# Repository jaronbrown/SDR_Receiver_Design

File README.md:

# Walla Walla University ENGR357 SDR Design Winter 2024

## Goals
- Continuous Coverage from 5-30 MHz and AM coverage (540-1700 kHz)
- Tune to AM by mixing up to 10.7 MHz then using the Tayloe detector to down-sample to 0-48 kHz

## Design
 - Incorporates a two stage mixing approach in order to achieve wider bandwidth with Si5351 quadrature limitations 
 - Utilizes a Tayloe detector for down-conversion of RF signals.
 - Optional second mixer to bring up AM frequencies (540-1700 kHz) so they can be sampled by Tayloe detector.
 - Input Stage: Automatic Band Pass Filters with optional AM mixer. Includes antenna ground isolation.
 - Output Stage: Quadrature signals amplified with 84 kHz low pass filter. Sampled directly with on-board ADC (48 kHz Nyquist) or output over 3.5mm audio jack. The larger LPF passband (84 kHz) minimizes ripple.
 - Raspberry Pi Pico W Controller with LDO (TPS7A8001DRBR) for cleaner +4V5 (derived from +5V USB).
 - H/W Controlled BPF multiplexors, i2c controlled 3-output VLO (Si5351), and i2s compatible ADC (PCM1808PWR).

## ltspice Simulations
Various core elements of the design were simulated to test their functionality. Notable simulations include a [Monte Carlo simulation](spice/BPF_monte_carlo.asc) of the three bandpass filters (frequency response shown below) to determine effects of component tolerances and a [simulation of the Tayloe detector](spice/Tayloe_test.asc), along with its "differential" amplifiers. The Tayloe detector input is a 1 $\mu V$ sinewave and the output (of the I channel) can be seen in the graph below. In the actual implementation, there is a 1 $\mu F$ blocking capacitor before the ADC and audio jack, but this is omitted for sake of simulation. This would remove the 2.25V DC offset.

Bandpass Filters

Tayloe Detector

## Fabrication Information
The boards tested were fabricated by [JLCPCB](jlcpcb.com). They also installed all the surface-mount components--LCSC part numbers included in schematic. Total fabrication cost (including building the boards) from JLCPCB was about $120 USD for 5 boards. The [build plan](BuildPlan.md) was followed for assembling the boards and testing their functionality. The specifications for the inductors and transformer used, can be found in [Inductors](Inductors.md).

## Software
### Python
The software for the Raspberry Pi Pico W consists of three microPython files: [main.py](python/main.py), [radio.py](python/radio.py), and [si5351.py](python/si5351.py). All three files should be loaded onto the Pico.

The microPython module to control the SI5351, [si5351.py](python/si5351.py), was provided by [https://github.com/thaaraak/Tinypico-Radio/tree/master](https://github.com/thaaraak/Tinypico-Radio/tree/master). Some minor changes were made to the ```outputs_enabled``` setter in order to allow individual clock enabling/disabling--used for the AM mixer local oscillator.

The radio control is handled by [radio.py](python/radio.py) which after initializing a ```Radio```, ```run()``` can be used to parse Quisk commands and automatically control bandpass filter selection (based on frequency) and frequency. The bandpass filters can also be controlled manually by entering "BAND,AUTO" to allow for manual testing and use of the built in bypass capacitor. Frequencies from 4-32 MHz are handled via the HF HIGH/LOW BPFs with a single stage of mixing. Frequencies from 0.4-4 MHz are handled via AM mixing (due to the SI5351 not maintaining quadrature below 4 MHz). When switching from AM bands back to HF the SI5351 control is reinitialized to prevent unpredictable clock drift.

Currently there is no support for WiFi control/data transmit, nor is there support for the on-board ADC. This would require migrating to C for DMA. This is coming soon TM.

## Quisk
This SDR is designed to be used with Quisk (https://james.ahlstrom.name/quisk/). Some basic Quisk device configs are provided in [quisk](quisk/). Currently there is no custom widget support for bandpass selection and AM offsets (for tuning away from center).

An optional [Dockerfile](Dockerfile) and sample [start script](startDocker.sh.sample) is provided to run Quisk via Docker--though this requires proper ```/dev/ttyACM0``` permissions, pulseaudio, and xserver. If running on Windows via WSL the aforementioned packages should be installed as well as utilizing usbipd-win (https://james.ahlstrom.name/quisk/) to passthrough the Pico connection.

## Case
stl files for a 3d printable [case](case) are included. Note that because the board does not have any mounting holes the case is a friction fit--consider adjusting tolerances when printing.

## Testing
Testing revealed the radio functions over the planned 10-30 MHz as well as the AM commercial frequencies (using the second mixer), though some signal overlap is apparent for AM. The bandpass filters were characterized using a signal generator and a spectrum analyzer.

### AM Bandpass Filter Characterization

### Low HF Bandpass Filter Characterization

### High HF Bandpass Filter Characterization

## KiCAD Schematic
### Complete Block Diagram

### Automatic Band Pass Filter

### AM Handling: Filters and Upconversion

### 3rd Order Butterworth BPF 5-18 MHz

### 3rd Order Butterworth BPF 13-32.7 MHz

### IQ Tayloe Detector & 84kHz IF filter

### SDR Controller

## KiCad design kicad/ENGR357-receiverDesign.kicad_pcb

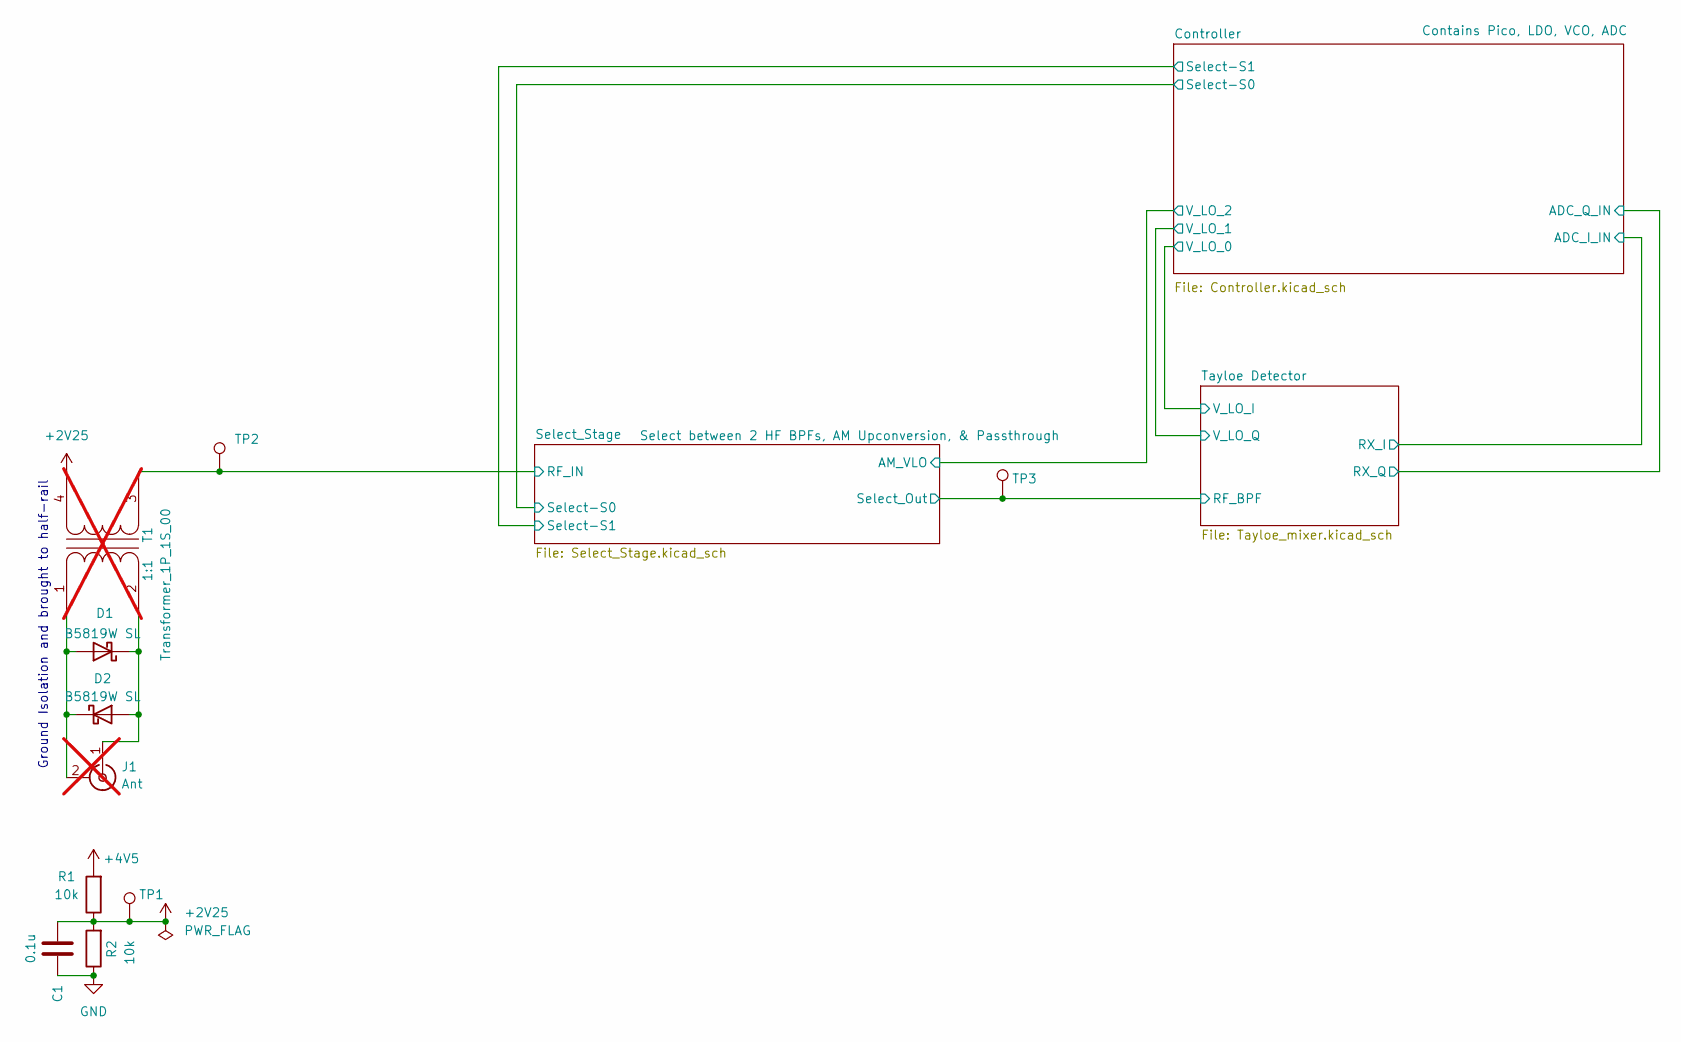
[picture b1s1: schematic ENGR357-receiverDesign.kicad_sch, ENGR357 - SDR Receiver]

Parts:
C1: 0.1u; C_0805_2012Metric; LCSC C49678
D1, D2: B5819W SL; D_SOD-123; LCSC C8598
J1: Ant; BNC_Amphenol_B6252HB-NPP3G-50_Horizontal; not fitted
R1, R2: 10k; R_0805_2012Metric; LCSC C17414
T1: Transformer_1P_1S_00; Transformer_Toroid_Horizontal_D10.5mm_Amidon-T37; not fitted
TP1, TP2, TP3: TestPoint; TestPoint_THTPad_D1.0mm_Drill0.5mm

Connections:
+2V25: C1.2, R1.1, R2.2, T1.4 (SB), TP1.1; also elsewhere on the board
+4V5: R1.2; also elsewhere on the board
/Select_Stage/RF_IN: T1.3 (SA), TP2.1; also elsewhere on the board
/Select_Stage/Select_Out: TP3.1; also elsewhere on the board
GND: C1.1, R2.1; also elsewhere on the board
unnamed: D1.2 (A), D2.1 (K), J1.2 (Ext), T1.1 (AA)
unnamed: D1.1 (K), D2.2 (A), J1.1 (In), T1.2 (AB)

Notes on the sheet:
Ground Isolation and brought to half-rail

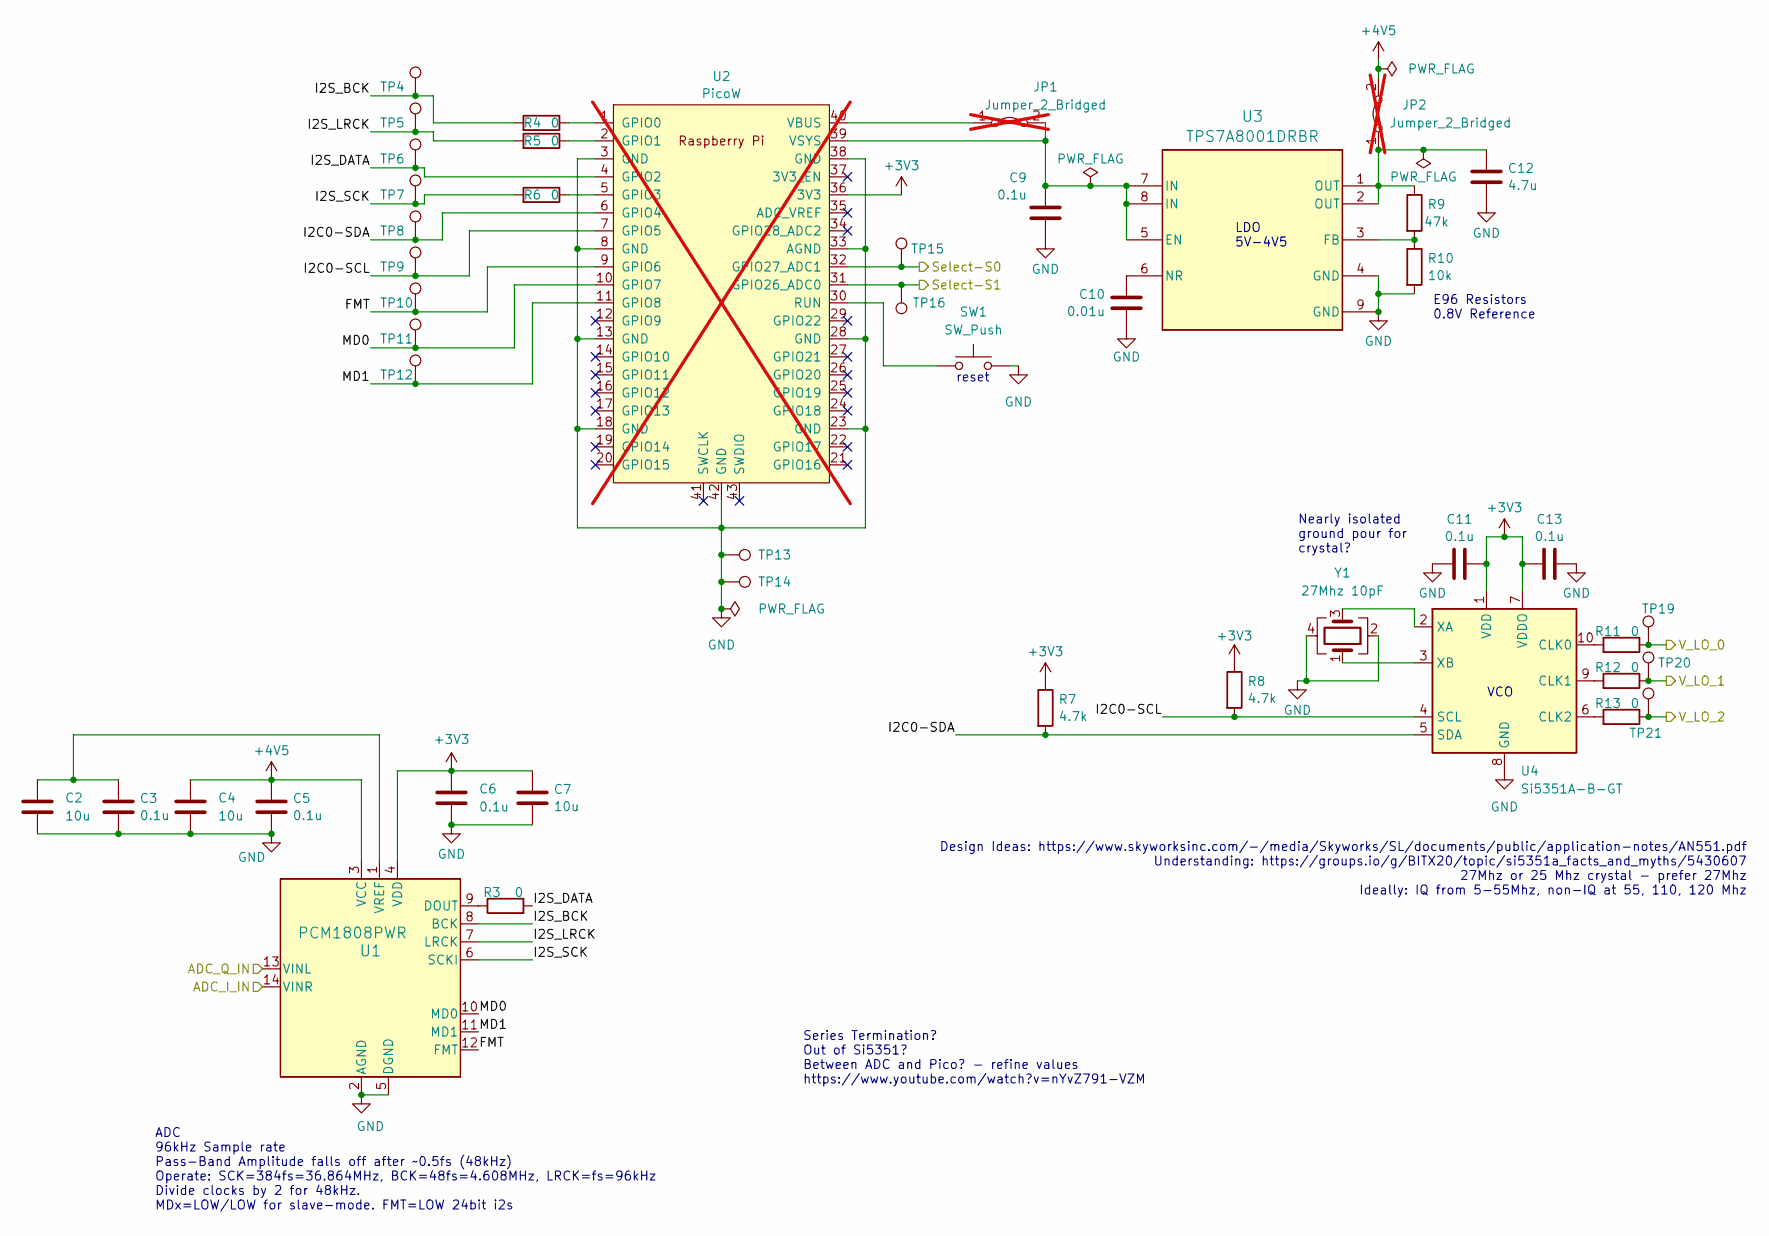
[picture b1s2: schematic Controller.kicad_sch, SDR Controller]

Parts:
C2, C4, C7: 10u; C_0805_2012Metric; LCSC C15850
C3, C5, C6, C9, C11, C13: 0.1u; C_0805_2012Metric; LCSC C49678
C10: 0.01u; C_0603_1608Metric; LCSC C57112
C12: 4.7u; C_0603_1608Metric; LCSC C19666
JP1, JP2: Jumper_2_Bridged; PinHeader_1x02_P2.54mm_Vertical; not fitted
R3, R4, R5, R6, R11, R12, R13: 0; R_0805_2012Metric; LCSC C17477
R7, R8: 4.7k; R_0805_2012Metric; LCSC C17673
R9: 47k; R_0805_2012Metric; LCSC C17713
R10: 10k; R_0805_2012Metric; LCSC C17414
SW1: SW_Push; SW_Push_1P1T_XKB_TS-1187A; LCSC C318884
TP4, TP5, TP6, TP7, TP8, TP9, TP10, TP11, TP12, TP13, TP14, TP15, TP16, TP19, TP20, TP21: TestPoint; TestPoint_THTPad_D1.0mm_Drill0.5mm
U1: PCM1808PWR; PW14; LCSC C55513
U2: PicoW; RPi_PicoW_SMD_TH; not fitted
U3: TPS7A8001DRBR; DRB0008A-MFG; LCSC C105265
U4: Si5351A-B-GT; MSOP-10_3x3mm_P0.5mm; LCSC C5451727
Y1: 27Mhz 10pF; Crystal_SMD_3225-4Pin_3.2x2.5mm; LCSC C5210645

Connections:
+3V3: C6.1, C7.1, C11.2, C13.1, R7.1, R8.1, U1.4 (VDD), U2.36 (3V3), U4.1 (VDD), U4.7 (VDDO); also elsewhere on the board
+4V5: C4.1, C5.1, JP2.2 (B), U1.3 (VCC); also elsewhere on the board
/Controller/ADC_I_IN: U1.14 (VINR); also elsewhere on the board
/Controller/ADC_Q_IN: U1.13 (VINL); also elsewhere on the board
/Controller/FMT: TP10.1, U1.12 (FMT), U2.9 (GPIO6); also elsewhere on the board
/Controller/I2C0-SCL: R8.2, TP9.1, U2.7 (GPIO5), U4.4 (SCL); also elsewhere on the board
/Controller/I2C0-SDA: R7.2, TP8.1, U2.6 (GPIO4), U4.5 (SDA); also elsewhere on the board
/Controller/I2S_BCK: R4.2, TP4.1, U1.8 (BCK)
/Controller/I2S_DATA: R3.2, TP6.1, U2.4 (GPIO2); also elsewhere on the board
/Controller/I2S_LRCK: R5.2, TP5.1, U1.7 (LRCK)
/Controller/I2S_SCK: R6.2, TP7.1, U1.6 (SCKI)
/Controller/MD0: TP11.1, U1.10 (MD0), U2.10 (GPIO7); also elsewhere on the board
/Controller/MD1: TP12.1, U1.11 (MD1), U2.11 (GPIO8); also elsewhere on the board
/Controller/Select-S0: TP15.1, U2.32 (GPIO27_ADC1); also elsewhere on the board
/Controller/Select-S1: TP16.1, U2.31 (GPIO26_ADC0); also elsewhere on the board
/Controller/V_LO_0: R11.1, TP19.1; also elsewhere on the board
/Controller/V_LO_1: R12.1, TP20.1; also elsewhere on the board
/Controller/V_LO_2: R13.1, TP21.1; also elsewhere on the board
GND: C2.2, C3.2, C4.2, C5.2, C6.2, C7.2, C9.2, C10.2, C11.1, C12.2, C13.2, R10.2, SW1.2, TP13.1, TP14.1, U1.2 (AGND), U1.5 (DGND), U2.3 (GND), U2.8 (GND), U2.13 (GND), U2.18 (GND), U2.23 (GND), U2.28 (GND), U2.33 (AGND), U2.38 (GND), U2.42 (GND), U3.4 (GND), U3.9 (GND), U4.8 (GND), Y1.2, Y1.4; also elsewhere on the board
unnamed 42: JP1.1 (A), U2.40 (VBUS); also elsewhere on the board
unnamed 43: C9.1, JP1.2 (B), U2.39 (VSYS), U3.5 (EN), U3.7 (IN), U3.8 (IN); also elsewhere on the board
unnamed: C12.1, JP2.1 (A), R9.1, U3.1 (OUT), U3.2 (OUT)
unnamed: R3.1, U1.9 (DOUT)
unnamed: C2.1, C3.1, U1.1 (VREF)
unnamed 50: R4.1, U2.1 (GPIO0); also elsewhere on the board
unnamed 51: R5.1, U2.2 (GPIO1); also elsewhere on the board
unnamed 52: R6.1, U2.5 (GPIO3); also elsewhere on the board
unnamed 53: SW1.1, U2.30 (RUN); also elsewhere on the board
unnamed: R9.2, R10.1, U3.3 (FB)
unnamed: C10.1, U3.6 (NR)
unnamed: R11.2, U4.10 (CLK0)
unnamed: R12.2, U4.9 (CLK1)
unnamed: R13.2, U4.6 (CLK2)
unnamed: U4.2 (XA), Y1.3
unnamed: U4.3 (XB), Y1.1

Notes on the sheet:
Nearly isolated ground pour for crystal?
LDO 5V-4V5
Series Termination? Out of Si5351? Between ADC and Pico? - refine values https://www.youtube.com/watch?v=nYvZ791-VZM
Design Ideas: https://www.skyworksinc.com/-/media/Skyworks/SL/documents/public/application-notes/AN551.pdf Understanding: https://groups.io/g/BITX20/topic/si5351a_facts_and_myths/5430607 27Mhz or 25 Mhz crystal - prefer 27Mhz Ideally: IQ from 5-55Mhz, non-IQ at 55, 110, 120 Mhz
reset
ADC 96kHz Sample rate Pass-Band Amplitude falls off after ~0.5fs (48kHz) Operate: SCK=384fs=36.864MHz, BCK=48fs=4.608MHz, LRCK=fs=96kHz Divide clocks by 2 for 48kHz. MDx=LOW/LOW for slave-mode. FMT=LOW 24bit i2s
VCO
E96 Resistors 0.8V Reference

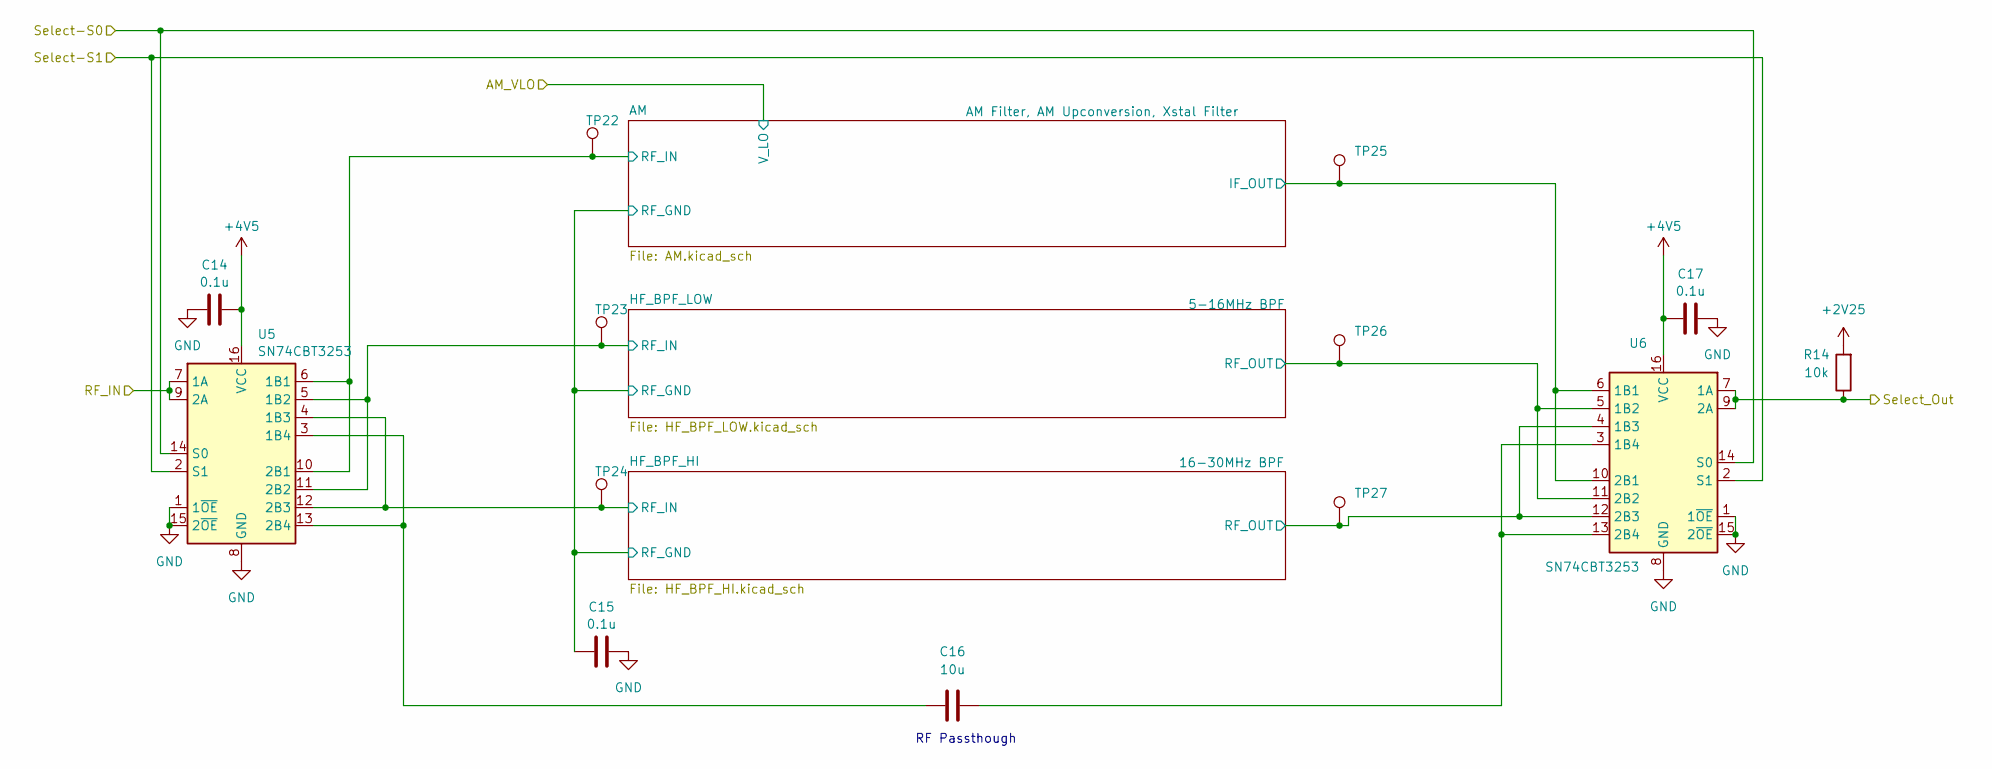
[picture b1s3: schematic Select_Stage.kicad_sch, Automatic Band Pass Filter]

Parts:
C14, C15, C17: 0.1u; C_0805_2012Metric; LCSC C49678
C16: 10u; C_0805_2012Metric; LCSC C15850
R14: 10k; R_0805_2012Metric; LCSC C17414
TP22, TP23, TP24, TP25, TP26, TP27: TestPoint; TestPoint_THTPad_D1.0mm_Drill0.5mm
U5, U6: SN74CBT3253; SOP65P640X120-16N; LCSC C2674672

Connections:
+2V25: R14.2; also elsewhere on the board
+4V5: C14.2, C17.2, U5.16 (VCC), U6.16 (VCC); also elsewhere on the board
/Controller/Select-S0: U5.14 (S0), U6.14 (S0); also elsewhere on the board
/Controller/Select-S1: U5.2 (S1), U6.2 (S1); also elsewhere on the board
/Select_Stage/AM/IF_OUT: TP25.1, U6.6 (1B1), U6.10 (2B1); also elsewhere on the board
/Select_Stage/AM/RF_GND: C15.1; also elsewhere on the board
/Select_Stage/AM/RF_IN: TP22.1, U5.6 (1B1), U5.10 (2B1); also elsewhere on the board
/Select_Stage/HF_BPF_HI/RF_IN: TP24.1, U5.4 (1B3), U5.12 (2B3); also elsewhere on the board
/Select_Stage/HF_BPF_HI/RF_OUT: TP27.1, U6.4 (1B3), U6.12 (2B3); also elsewhere on the board
/Select_Stage/HF_BPF_LOW/RF_IN: TP23.1, U5.5 (1B2), U5.11 (2B2); also elsewhere on the board
/Select_Stage/HF_BPF_LOW/RF_OUT: TP26.1, U6.5 (1B2), U6.11 (2B2); also elsewhere on the board
/Select_Stage/RF_IN: U5.7 (1A), U5.9 (2A); also elsewhere on the board
/Select_Stage/Select_Out: R14.1, U6.7 (1A), U6.9 (2A); also elsewhere on the board
GND: C14.1, C15.2, C17.1, U5.1 (1~OE), U5.8 (GND), U5.15 (2~OE), U6.1 (1~OE), U6.8 (GND), U6.15 (2~OE); also elsewhere on the board
unnamed: C16.1, U5.3 (1B4), U5.13 (2B4)
unnamed: C16.2, U6.3 (1B4), U6.13 (2B4)

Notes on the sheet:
RF Passthough

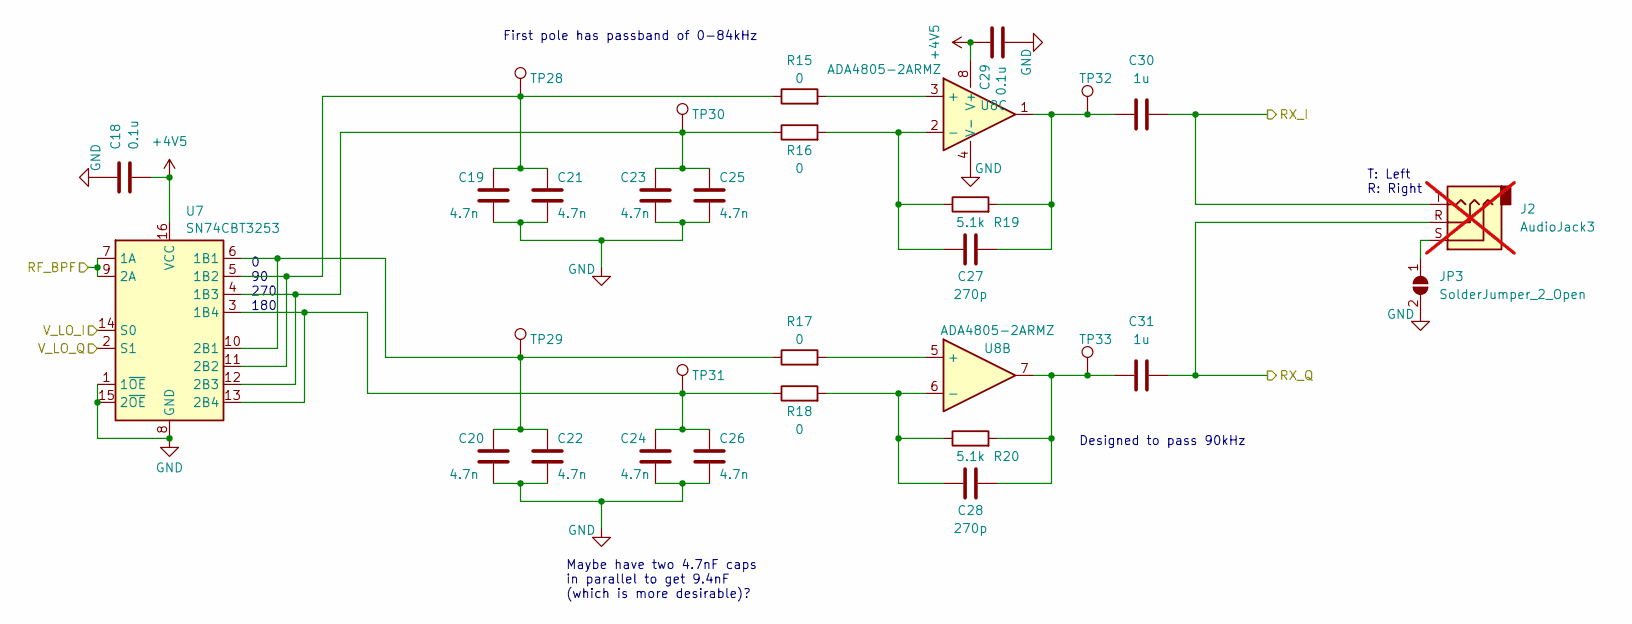
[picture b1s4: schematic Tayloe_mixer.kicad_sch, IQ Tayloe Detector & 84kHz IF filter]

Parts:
C18, C29: 0.1u; C_0805_2012Metric; LCSC C49678
C19, C20, C21, C22, C23, C24, C25, C26: 4.7n; C_0603_1608Metric; LCSC C883564
C27, C28: 270p; C_0402_1005Metric; LCSC C881990
C30, C31: 1u; C_0805_2012Metric; LCSC C28323
J2: AudioJack3; Jack_3.5mm_CUI_SJ1-3523N_Horizontal; not fitted
JP3: SolderJumper_2_Open; SolderJumper-2_P1.3mm_Open_RoundedPad1.0x1.5mm
R15, R16, R17, R18: 0; R_0805_2012Metric; LCSC C17477
R19, R20: 5.1k; R_0805_2012Metric; LCSC C27834
TP28, TP29, TP30, TP31, TP32, TP33: TestPoint; TestPoint_THTPad_D1.0mm_Drill0.5mm
U7: SN74CBT3253; SOP65P640X120-16N; LCSC C2674672
U8: ADA4805-2ARMZ; MSOP-8_3x3mm_P0.65mm; LCSC C208293

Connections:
+4V5: C18.2, C29.1, U7.16 (VCC), U8.8 (V+); also elsewhere on the board
/Controller/ADC_I_IN: C30.2, J2.T; also elsewhere on the board
/Controller/ADC_Q_IN: C31.2, J2.R; also elsewhere on the board
/Controller/V_LO_0: U7.14 (S0); also elsewhere on the board
/Controller/V_LO_1: U7.2 (S1); also elsewhere on the board
/Select_Stage/Select_Out: U7.7 (1A), U7.9 (2A); also elsewhere on the board
GND: C18.1, C19.2, C20.2, C21.2, C22.2, C23.2, C24.2, C25.2, C26.2, C29.2, JP3.2 (B), U7.1 (1~OE), U7.8 (GND), U7.15 (2~OE), U8.4 (V-); also elsewhere on the board
unnamed: C27.2, C30.1, R19.2, TP32.1, U8.1
unnamed: C28.2, C31.1, R20.2, TP33.1, U8.7
unnamed 45: J2.S, JP3.1 (A); also elsewhere on the board
unnamed: C20.1, C22.1, R17.1, TP29.1, U7.6 (1B1), U7.10 (2B1)
unnamed: C19.1, C21.1, R15.1, TP28.1, U7.5 (1B2), U7.11 (2B2)
unnamed: C23.1, C25.1, R16.1, TP30.1, U7.4 (1B3), U7.12 (2B3)
unnamed: C24.1, C26.1, R18.1, TP31.1, U7.3 (1B4), U7.13 (2B4)
unnamed: R15.2, U8.3 (+)
unnamed: C27.1, R16.2, R19.1, U8.2 (-)
unnamed: R17.2, U8.5 (+)
unnamed: C28.1, R18.2, R20.1, U8.6 (-)

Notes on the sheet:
First pole has passband of 0-84kHz
Maybe have two 4.7nF caps in parallel to get 9.4nF (which is more desirable)?
Designed to pass 90kHz
T: Left R: Right
0 90 270 180

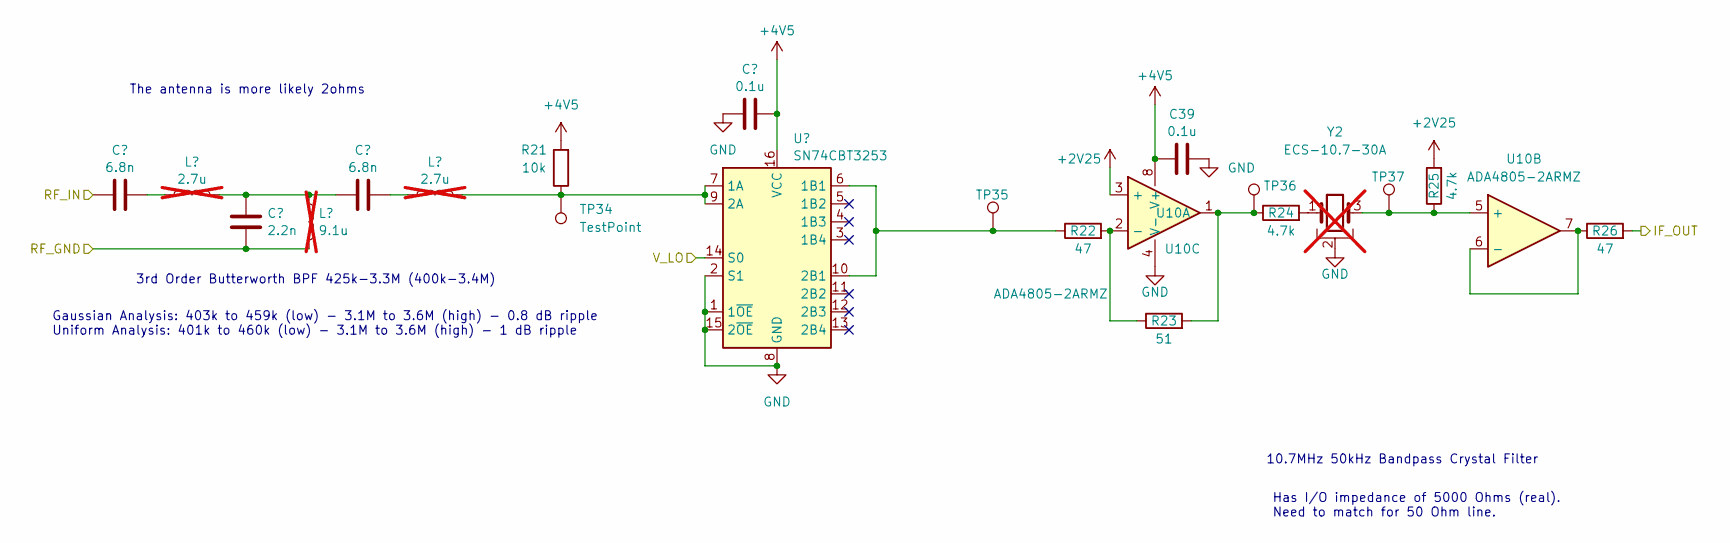
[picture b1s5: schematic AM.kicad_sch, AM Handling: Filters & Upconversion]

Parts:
C35, C37: 6.8n; C_0603_1608Metric; LCSC C1631
C36: 2.2n; C_0805_2012Metric; LCSC C28260
C38, C39: 0.1u; C_0805_2012Metric; LCSC C49678
L4, L6: 2.7u; L_Toroid_Vertical_L10.0mm_W5.0mm_P5.08mm; not fitted
L5: 9.1u; L_Toroid_Vertical_L10.0mm_W5.0mm_P5.08mm; not fitted
R21: 10k; R_0805_2012Metric; LCSC C17414
R22, R26: 47; R_0805_2012Metric; LCSC C17714
R23: 51; R_0805_2012Metric; LCSC C17738
R24, R25: 4.7k; R_0805_2012Metric; LCSC C17673
TP34, TP35, TP36, TP37: TestPoint; TestPoint_THTPad_D1.0mm_Drill0.5mm
U9: SN74CBT3253; SOP65P640X120-16N; LCSC C2674672
U10: ADA4805-2ARMZ; MSOP-8_3x3mm_P0.65mm; LCSC C208293
Y2: ECS-10.7-30A; Crystal_HC49-U-3Pin_Vertical; not fitted

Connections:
+2V25: R25.2, U10.3 (+); also elsewhere on the board
+4V5: C38.2, C39.1, R21.2, U9.16 (VCC), U10.8 (V+); also elsewhere on the board
/Controller/V_LO_2: U9.14 (S0); also elsewhere on the board
/Select_Stage/AM/IF_OUT: R26.2; also elsewhere on the board
/Select_Stage/AM/RF_GND: C36.2, L5.2; also elsewhere on the board
/Select_Stage/AM/RF_IN: C35.2; also elsewhere on the board
GND: C38.1, C39.2, U9.1 (1~OE), U9.2 (S1), U9.8 (GND), U9.15 (2~OE), U10.4 (V-), Y2.2; also elsewhere on the board
unnamed: C35.1, L4.1
unnamed: C36.1, C37.1, L4.2, L5.1
unnamed: C37.2, L6.1
unnamed 46: R23.2, R24.1, TP36.1, U10.1; also elsewhere on the board
unnamed: R24.2, Y2.1
unnamed: L6.2, R21.1, TP34.1, U9.7 (1A), U9.9 (2A)
unnamed: R22.1, TP35.1, U9.6 (1B1), U9.10 (2B1)
unnamed: R22.2, R23.1, U10.2 (-)
unnamed 74: R25.1, TP37.1, U10.5 (+), Y2.3; also elsewhere on the board
unnamed: R26.1, U10.6 (-), U10.7

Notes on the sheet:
Has I/O impedance of 5000 Ohms (real). Need to match for 50 Ohm line.
10.7MHz 50kHz Bandpass Crystal Filter
3rd Order Butterworth BPF 425k-3.3M (400k-3.4M)
The antenna is more likely 2ohms
Gaussian Analysis: 403k to 459k (low) - 3.1M to 3.6M (high) - 0.8 dB ripple Uniform Analysis: 401k to 460k (low) - 3.1M to 3.6M (high) - 1 dB ripple

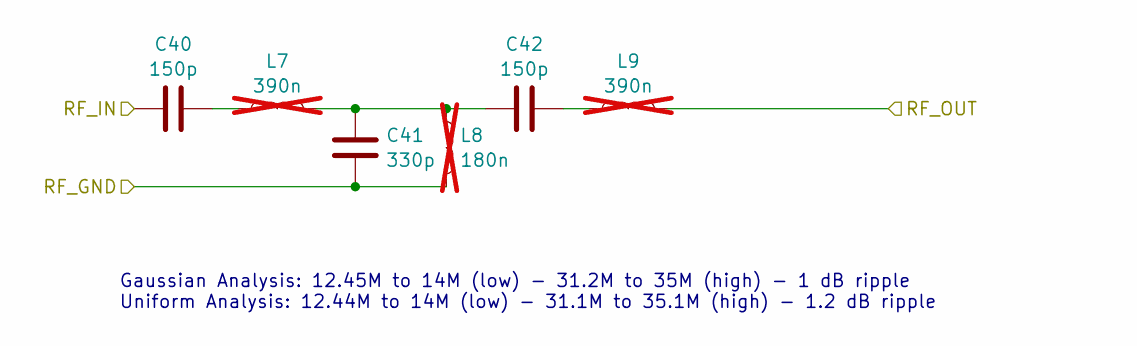
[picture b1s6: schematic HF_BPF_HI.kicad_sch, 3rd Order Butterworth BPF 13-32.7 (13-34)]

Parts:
C40, C42: 150p; C_0603_1608Metric; LCSC C1594
C41: 330p; C_0603_1608Metric; LCSC C1664
L7, L9: 390n; L_Toroid_Vertical_L10.0mm_W5.0mm_P5.08mm; not fitted
L8: 180n; L_Toroid_Vertical_L10.0mm_W5.0mm_P5.08mm; not fitted

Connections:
/Select_Stage/AM/RF_GND: C41.2, L8.2; also elsewhere on the board
/Select_Stage/HF_BPF_HI/RF_IN: C40.2; also elsewhere on the board
/Select_Stage/HF_BPF_HI/RF_OUT: L9.2; also elsewhere on the board
unnamed: C40.1, L7.1
unnamed: C41.1, C42.1, L7.2, L8.1
unnamed: C42.2, L9.1

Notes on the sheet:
Gaussian Analysis: 12.45M to 14M (low) - 31.2M to 35M (high) - 1 dB ripple Uniform Analysis: 12.44M to 14M (low) - 31.1M to 35.1M (high) - 1.2 dB ripple

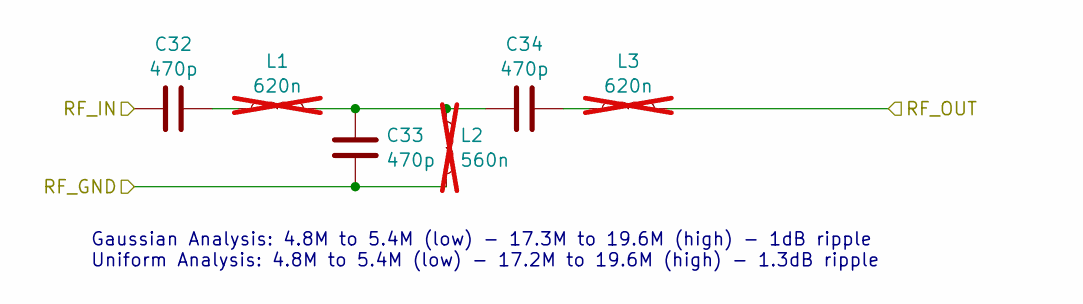
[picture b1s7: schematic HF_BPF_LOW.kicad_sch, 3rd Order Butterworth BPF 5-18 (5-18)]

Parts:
C32, C33, C34: 470p; C_0805_2012Metric; LCSC C1743
L1, L3: 620n; L_Toroid_Vertical_L10.0mm_W5.0mm_P5.08mm; not fitted
L2: 560n; L_Toroid_Vertical_L10.0mm_W5.0mm_P5.08mm; not fitted

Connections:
/Select_Stage/AM/RF_GND: C33.2, L2.2; also elsewhere on the board
/Select_Stage/HF_BPF_LOW/RF_IN: C32.2; also elsewhere on the board
/Select_Stage/HF_BPF_LOW/RF_OUT: L3.2; also elsewhere on the board
unnamed: C32.1, L1.1
unnamed: C33.1, C34.1, L1.2, L2.1
unnamed: C34.2, L3.1

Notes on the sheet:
Gaussian Analysis: 4.8M to 5.4M (low) - 17.3M to 19.6M (high) - 1dB ripple Uniform Analysis: 4.8M to 5.4M (low) - 17.2M to 19.6M (high) - 1.3dB ripple

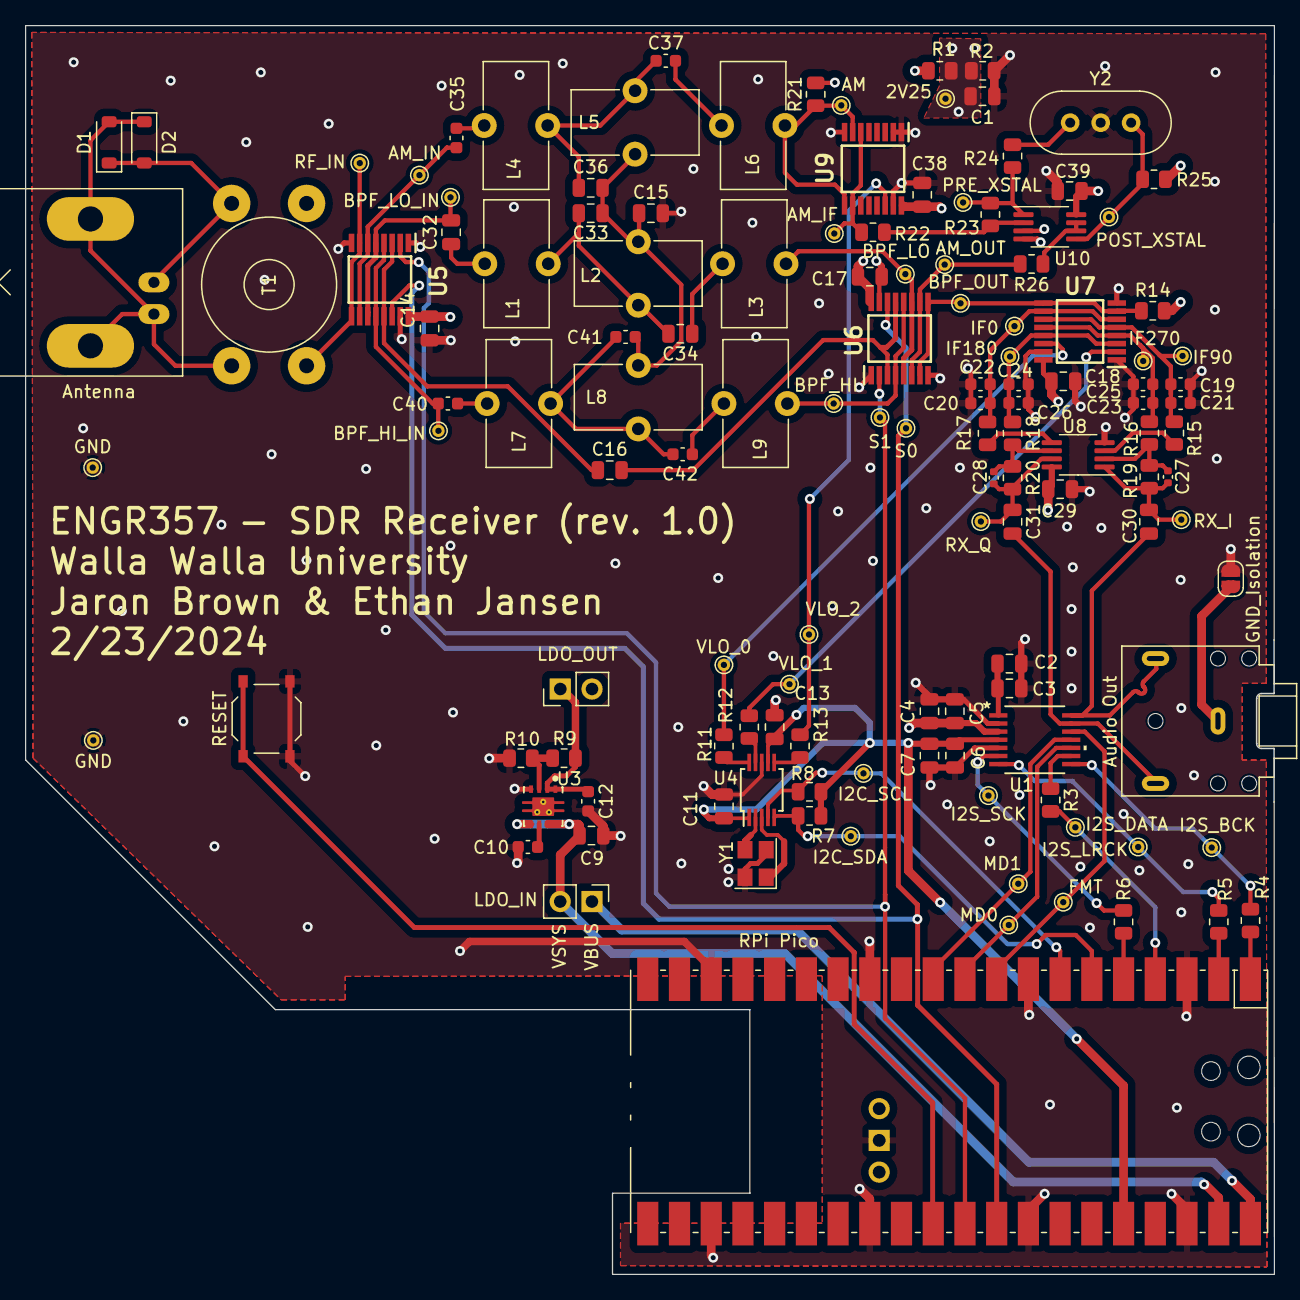
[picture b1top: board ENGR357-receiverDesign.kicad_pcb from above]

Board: 4 copper layers, 100.0 x 100.0 mm, 132 parts (0 on the bottom side), 76 nets.

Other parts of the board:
Audio Out: AudioJack3; Jack_3.5mm_CUI_SJ1-3523N_Horizontal
POST_XSTAL: TestPoint; TestPoint_THTPad_D1.0mm_Drill0.5mm
PRE_XSTAL: TestPoint; TestPoint_THTPad_D1.0mm_Drill0.5mm
RPi Pico: PicoW; RPi_PicoW_SMD_TH

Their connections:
+3V3: RPi Pico.36 (3V3); also elsewhere on the board
/Controller/ADC_I_IN: Audio Out.T; also elsewhere on the board
/Controller/ADC_Q_IN: Audio Out.R; also elsewhere on the board
/Controller/FMT: RPi Pico.9 (GPIO6); also elsewhere on the board
/Controller/I2C0-SCL: RPi Pico.7 (GPIO5); also elsewhere on the board
/Controller/I2C0-SDA: RPi Pico.6 (GPIO4); also elsewhere on the board
/Controller/I2S_DATA: RPi Pico.4 (GPIO2); also elsewhere on the board
/Controller/MD0: RPi Pico.10 (GPIO7); also elsewhere on the board
/Controller/MD1: RPi Pico.11 (GPIO8); also elsewhere on the board
/Controller/Select-S0: RPi Pico.32 (GPIO27_ADC1); also elsewhere on the board
/Controller/Select-S1: RPi Pico.31 (GPIO26_ADC0); also elsewhere on the board
GND: RPi Pico.3 (GND), RPi Pico.8 (GND), RPi Pico.13 (GND), RPi Pico.18 (GND), RPi Pico.23 (GND), RPi Pico.28 (GND), RPi Pico.33 (AGND), RPi Pico.38 (GND), RPi Pico.42 (GND); also elsewhere on the board
unnamed 42: RPi Pico.40 (VBUS); also elsewhere on the board
unnamed 43: RPi Pico.39 (VSYS); also elsewhere on the board
unnamed 45: Audio Out.S; also elsewhere on the board
unnamed 46: PRE_XSTAL.1; also elsewhere on the board
unnamed 50: RPi Pico.1 (GPIO0); also elsewhere on the board
unnamed 51: RPi Pico.2 (GPIO1); also elsewhere on the board
unnamed 52: RPi Pico.5 (GPIO3); also elsewhere on the board
unnamed 53: RPi Pico.30 (RUN); also elsewhere on the board
unnamed 74: POST_XSTAL.1; also elsewhere on the board

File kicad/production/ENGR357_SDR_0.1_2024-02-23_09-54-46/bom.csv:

Designator,Footprint,Quantity,Value,LCSC Part #
"C1, C11, C13, C14, C15, C17, C18, C29, C3, C38, C39, C5, C6, C9",0805,14,0.1u,C49678
C10,0603,1,0.01u,C57112
C12,0603,1,4.7u,C19666
"C16, C2, C4, C7",0805,4,10u,C15850
"C19, C20, C21, C22, C23, C24, C25, C26",0603,8,4.7n,C883564
"C27, C28",0402,2,270p,C881990
"C30, C31",0805,2,1u,C28323
"C32, C33, C34",0805,3,470p,C1743
"C35, C37",0603,2,6.8n,C1631
C36,0805,1,2.2n,C28260
"C40, C42",0603,2,150p,C1594
C41,0603,1,330p,C1664
"D1, D2",D_SOD-123,2,B5819W SL,C8598
JP3,SolderJumper-2_P1.3mm_Open_RoundedPad1.0x1.5mm,1,GND_Isolation,
"POST_XSTAL, PRE_XSTAL, TP1, TP10, TP11, TP12, TP13, TP14, TP15, TP16, TP19, TP2, TP20, TP21, TP22, TP23, TP24, TP25, TP26, TP27, TP28, TP29, TP3, TP30, TP31, TP32, TP33, TP34, TP35, TP4, TP5, TP6, TP7, TP8, TP9",TestPoint_THTPad_D1.0mm_Drill0.5mm,35,TestPoint,
"R1, R10, R14, R2, R21",0805,5,10k,C17414
"R11, R12, R13, R15, R16, R17, R18, R3, R4, R5, R6",0805,11,0,C17477
"R19, R20",0805,2,5.1k,C27834
"R22, R26",0805,2,47,C17714
R23,0805,1,51,C17738
"R24, R25, R7, R8",0805,4,4.7k,C17673
R9,0805,1,47k,C17713
SW1,SW_Push_1P1T_XKB_TS-1187A,1,SW_Push,C318884
U1,PW14,1,PCM1808PWR,C55513
"U10, U8",MSOP-8_3x3mm_P0.65mm,2,ADA4805-2ARMZ,C208293
U3,DRB0008A-MFG,1,TPS7A8001DRBR,C105265
U4,MSOP-10_3x3mm_P0.5mm,1,Si5351A-B-GT,C5451727
"U5, U6, U7, U9",SOP65P640X120-16N,4,SN74CBT3253,C2674672
Y1,Crystal_SMD_3225-4Pin_3.2x2.5mm,1,27Mhz 10pF,C5210645

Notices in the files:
kicad/VGA-PicoW/picow_vga_sd_aud.kicad_sch:
(c) 2022 Raspberry Pi Ltd
